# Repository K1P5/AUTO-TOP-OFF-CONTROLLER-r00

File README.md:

# AUTO-TOP-OFF-CONTROLLER-r00
WITH ADDITIONAL TWIN RELAYS FOR RODI CONTROL

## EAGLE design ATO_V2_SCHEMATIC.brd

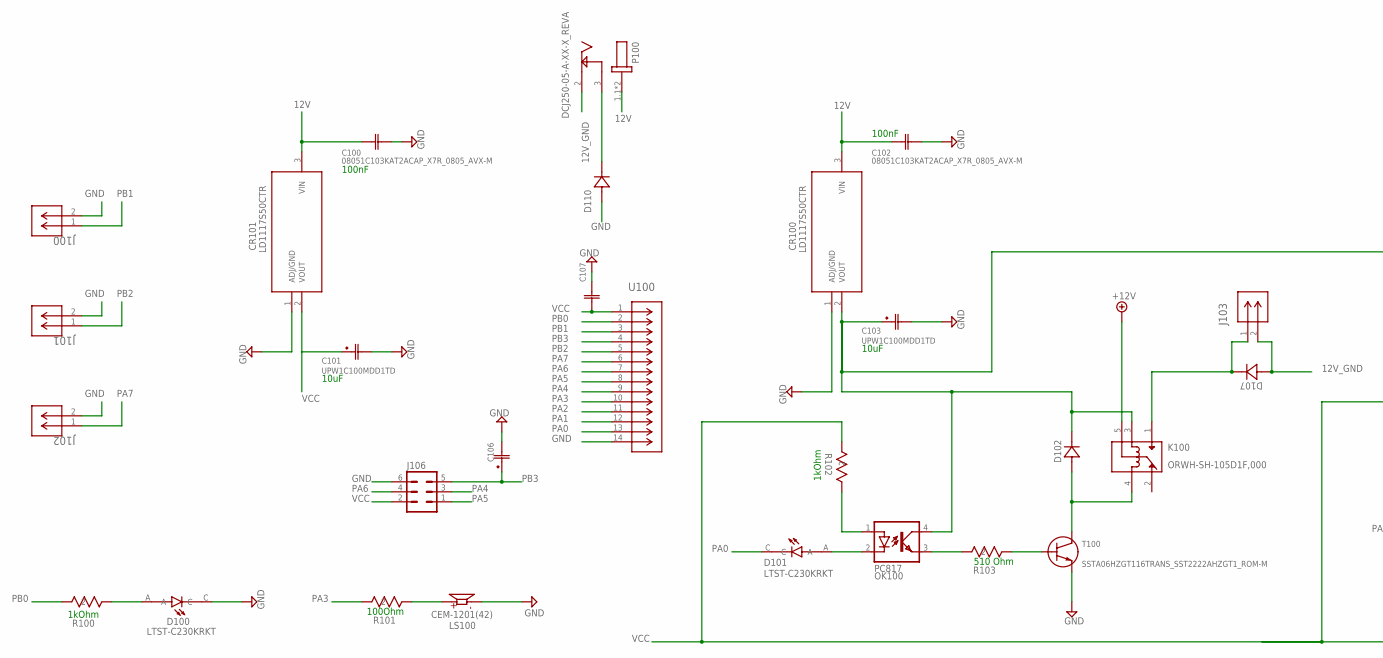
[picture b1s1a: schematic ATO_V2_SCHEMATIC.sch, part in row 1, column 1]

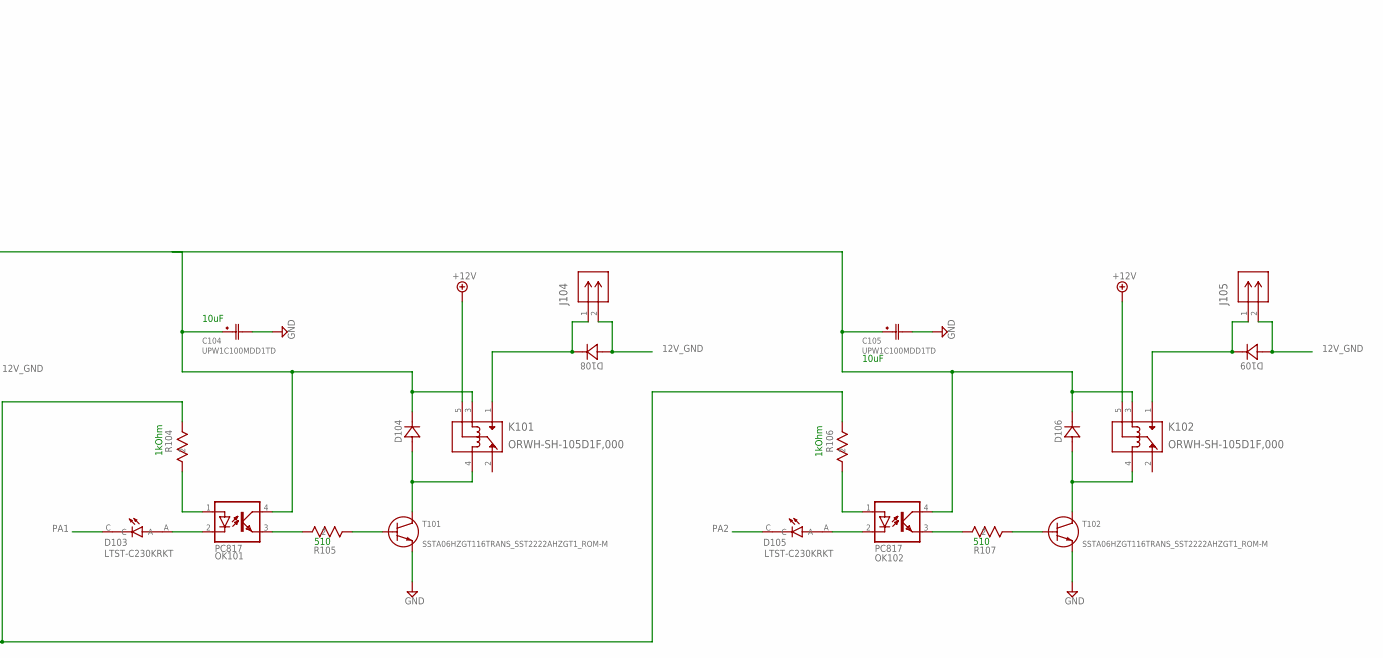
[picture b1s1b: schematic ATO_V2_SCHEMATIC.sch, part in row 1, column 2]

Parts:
C100, C102, C107: 08051C103KAT2ACAP_X7R_0805_AVX-M; CAP_X7R_0805_AVX-M
C101, C103, C104, C105, C106: UPW1C100MDD1TD; CAP_UEP_5X11_NCH
CR100, CR101: LD1117S50CTR; SOT-223_STM
D100, D101, D103, D105: LTST-C230KRKT; LEDC3216X110
D102, D104, D106, D107, D108, D109, D110: 1SMB5922B-13; SMB_DIO
J100, J101, J102, J103, J104, J105: B2B-XH-A(LF)(SN); CONN_B2B-XH-A(LF)(SN)_JST
J106: MA03-2
K100, K101, K102: ORWH-SH-105D1F,000; RELAY_1-1721150-0_TEC
LS100: CEM-1201(42); CUI_CEM-1201(42)
OK100, OK101, OK102: PC817; DIL04
P100: DCJ250-05-A-XX-X_REVA; GCT_DCJ250-05-A-XX-X_REVA
R100, R101, R102, R103, R104, R105, R106, R107: CRCW0805510RJNEA; RC0805N_VIS
T100, T101, T102: SSTA06HZGT116TRANS_SST2222AHZGT1_ROM-M; TRANS_SST2222AHZGT1_ROM-M
U100: 1-2199298-3; CONN14_1-2199298-3_TEC

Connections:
12V: C100.1, C102.1, CR100.3 (VIN), CR101.3 (VIN), K100.5, K101.5, K102.5, P100.1.1 (1), P100.1.2 (1)
12V_GND: D107.2, D108.2, D109.2, D110.1, J103.2, J104.2, J105.2, P100.2, P100.3
GND: C100.2, C101.2, C102.2, C103.2, C104.2, C105.2, C106.2, C107.2, CR100.1 (ADJ/GND), CR101.1 (ADJ/GND), D100.C, D110.2, J100.2, J101.2, J102.2, J106.6, LS100.M, T100.2 (11), T101.2 (11), T102.2 (11), U100.14
unnamed: OK100.3 (EMIT), R103.2
unnamed: D101.A, OK100.2 (C)
unnamed: D104.2, K101.4, T101.3 (13)
unnamed: D102.2, K100.4, T100.3 (13)
unnamed: OK100.1 (A), R102.1
unnamed: R103.1, T100.1 (12)
unnamed: D100.A, R100.1
unnamed: C103.1, C104.1, C105.1, CR100.2 (VOUT), D102.1, D104.1, D106.1, K100.3, K101.3, K102.3, OK100.4 (COL), OK101.4 (COL), OK102.4 (COL)
unnamed: D107.1, J103.1, K100.1
unnamed: D103.A, OK101.2 (C)
unnamed: OK101.1 (A), R104.2
unnamed: OK101.3 (EMIT), R105.2
unnamed: R105.1, T101.1 (12)
unnamed: D108.1, J104.1, K101.1
unnamed: D106.2, K102.4, T102.3 (13)
unnamed: D105.A, OK102.2 (C)
unnamed: OK102.1 (A), R106.2
unnamed: OK102.3 (EMIT), R107.2
unnamed: R107.1, T102.1 (12)
unnamed: D109.1, J105.1, K102.1
unnamed: LS100.P, R101.1
PA0: D101.C, U100.13
PA1: D103.C, U100.12
PA2: D105.C, U100.11
PA3: R101.2, U100.10
PA4: J106.3, U100.9
PA5: J106.1, U100.8
PA6: J106.4, U100.7
PA7: J102.1, U100.6
PB0: R100.2, U100.2
PB1: J100.1, U100.3
PB2: J101.1, U100.5
PB3: C106.1, J106.5, U100.4
VCC: C101.1, C107.1, CR101.2 (VOUT), J106.2, R102.2, R104.1, R106.1, U100.1

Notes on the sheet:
1kOhm
510 Ohm
10uF
100nF
510
100Ohm

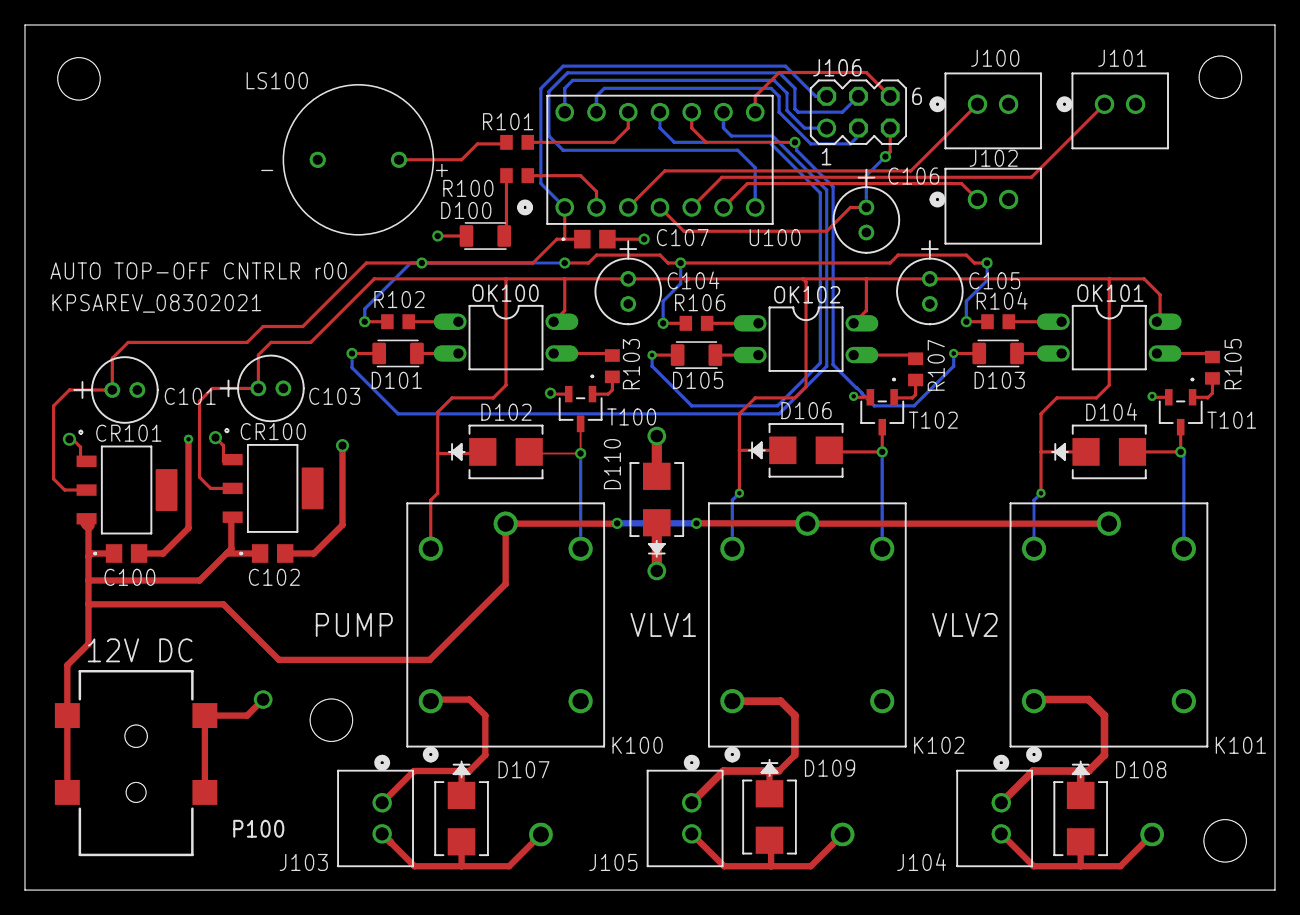
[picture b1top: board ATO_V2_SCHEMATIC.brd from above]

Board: 2 copper layers, 100.0 x 69.2 mm, 48 parts (0 on the bottom side), 37 nets.

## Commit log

2021-09-02 Added ATO r00 .brd file
2021-09-03 Added ATO r00 Schematic.
2021-09-03 Gerber file initial release.

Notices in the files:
parts and their libraries:
COPYRIGHT: Copyright (C) 2021 Ultra Librarian. All rights reserved.
